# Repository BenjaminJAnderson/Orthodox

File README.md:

# ORTHODOX

A custom ortholinear mechanical keyboard comprising a 60-key, two-layer PCB designed in KiCad, a FreeCAD case and parametric OpenSCAD keycaps. The design uses Kailh Choc switches, per-key diodes and USB-C, with copper coil footprints reserved for future analogue sensing.

## Overview

Orthodox is a design archive for a compact ortholinear keyboard. Its grid layout removes the row offsets of a conventional staggered keyboard, simplifying both the keycap geometry and the electrical matrix. The repository contains the KiCad schematic and PCB, manufacturing exports, a FreeCAD case model and a parametric keycap generator.

This repository covers the hardware and mechanical design. Firmware is not included, the LDC1614 inductive-sensing circuit is planned but not present on this PCB revision, and no fabrication, assembly or measurement results are recorded. The files are useful as a reference design or starting point for further work, not as a verified build guide.

## Features

- **60-key ortholinear matrix:** thirteen columns and five rows, including 2u keys, a 6u spacebar and smaller 0.5u keycaps.
- **Per-key diodes:** sixty 1206 surface-mount diodes, one for each switch position.
- **ATmega32U4 controller:** a TQFP-44 ATmega32U4-A with a four-pad crystal, reset circuit and decoupling.
- **USB-C connection:** a GCT USB4055-30-A receptacle wired for USB 2.0 data and power.
- **Kailh Choc footprints:** 1u, 2u and 6u switch positions using Kailh Choc V1 footprints, plus compact 58-series footprints for the smallest keys.
- **Coil-enabled key positions:** eight switch footprints on W, A, S, D and the four arrow keys include dual-layer copper spirals for future inductive sensing.
- **Two-layer PCB:** 1.6 mm FR4, approximately 253.15 x 100.75 mm, with 467 routed track segments and 23 vias.
- **Manufacturing exports:** Gerber, drill and job files in `Hardware/PCB/export/`, plus a STEP model of the board.
- **FreeCAD case model:** a Part Design body measuring approximately 259.26 x 107 x 20 mm.
- **Parametric keycaps:** a KeyV2-based OpenSCAD generator with per-key positions, sizes, heights and five legend layers.
- **Coil generator:** a Python script that emits KiCad track segments for the spiral coils.

## Technologies

- **KiCad:** schematic capture, PCB layout, design rules, 3D preview and Gerber generation.
- **FreeCAD:** parametric case modelling with sketches, pads, pockets and chamfers.
- **OpenSCAD and KeyV2:** parametric keycap geometry, legends and STL export.
- **Python 3:** generation of the Archimedean spiral tracks used by the coil footprints.
- **ATmega32U4:** the USB-capable AVR microcontroller at the centre of the board.
- **Kailh Choc V1 and 58-series switches:** switch footprints used by the PCB.
- **USB-C:** the board's power and data connector.
- **LDC1614 (planned):** the intended inductive-sensing device for the coil-equipped keys, not yet implemented on the PCB.

## Gallery

The PCB layout shows the 13-column matrix, eight spiral coil footprints, the ATmega32U4 and the USB-C connector.

The schematic covers the USB-C interface, crystal, reset circuit, decoupling and the ATmega32U4 pin assignments.

The matrix uses thirteen column nets and five row nets, with one diode per switch.

The keycap layout includes mixed key sizes, smaller 0.5u keys and multiple legend positions.

The FreeCAD case model provides the outer enclosure around the PCB and keycap assembly.

## Technical details

### PCB and matrix

The board uses thirteen column nets, `COL0` to `COL12`, and five row nets, `ROW0` to `ROW4`, with one 1206 diode in series with each switch. Sixty switch positions are placed in the layout. The controller is an ATmega32U4-A in a TQFP-44 package. USB-C is wired for USB 2.0, with 22R series resistors on the data lines, a crystal with 22 pF load capacitors, a reset switch and a 10 kΩ pull-up on the reset line.

The board is a two-layer, 1.6 mm FR4 design measuring approximately 253.15 x 100.75 mm. The routed board contains 467 track segments and 23 vias. An online view of the board is available on [CADLAB.io](https://cadlab.io/project/25013).

### Inductive coil footprints

Eight switch positions, covering W, A, S, D and the four arrow keys, use special footprints containing a copper spiral around the switch centre. The spiral is drawn on both copper layers and uses 0.15 mm tracks with 0.30 mm spacing over eight turns. Each footprint adds two small SMD pads, numbered 3 and 4, for the coil terminals.

`Software/spiral.py` generates the spiral as individual KiCad `segment` entries and prints them to standard output. The radius, number of sides, track width, track spacing, turn count and layer can be changed at the bottom of the script. The design stops at the coil footprint: the schematic includes a two-pin `Coil` connector (`J2`), but no LDC1614 or other inductive-sensing IC is placed on the board.

### Case

`Hardware/Model/Keyboard/Keyboard.FCStd` contains a FreeCAD Part Design body with a sketch, pad, pocket and chamfer. Its outer envelope is approximately 259.26 x 107 x 20 mm. The repository does not include separate fabrication drawings or fit measurements for the case.

### Keycaps

`Hardware/Model/Keycaps/OrthodoxLayout.scad` is built on [KeyV2](https://github.com/rsheldiii/openSCAD-projects). It defines the position, width, height and legend of every key using explicit arrays, including the 2u keys, 6u spacebar and 0.5u keys. Five nested `legend()` calls place primary, function-key, symbol and shift legends at different positions on each keycap.

The layout uses the low-profile transformation, bar supports, an 18.16 mm base width and a nominal 11.5 mm total depth before the low-profile transformation. The included `OrthodoxLayout.stl` is a pre-exported model spanning approximately 247 x 94 x 8 mm. The layout file contains a commented `$stem_type = "choc"` setting; uncomment it before export to generate stems for the Choc switches.

## Challenges and solutions

### Integrating coils into switch footprints

- **Problem:** The analogue keys need a planar coil under each switch, but the switch cutout, central hole and electrical pads occupy the middle of the footprint.
- **Approach:** `spiral.py` generates the coil as many short KiCad track segments. These are embedded directly in a modified Kailh Choc footprint, using a larger pad arrangement and a spiral that surrounds the switch centre on both copper layers.
- **Outcome:** Eight coil-enabled footprints exist in the PCB layout. The sensing IC and its supporting circuit remain unbuilt, so the coil geometry has not been electrically validated.

### Placing multiple legends on small keycaps

- **Problem:** KeyV2's `legend()` module is designed around a single legend per keycap, while the Orthodox layout needs several legends on many keys.
- **Approach:** The layout nests five `legend()` calls with separate arrays for the centre, bottom-left, bottom-right, top-left and top-right positions. Font sizes and offsets are defined per key, including the smaller 0.5u keys.
- **Outcome:** A single OpenSCAD file produces the full 60-key layout and an STL export. The commit history records an attempt to add Font Awesome glyphs and notes that multiple-font rendering still needed investigation.

### Mixing key sizes in a regular grid

- **Problem:** An ortholinear grid is regular, but the design mixes 1u, 2u, 6u and 0.5u keys, so a single uniform array cannot describe the layout.
- **Approach:** The keycap generator stores explicit x/y positions, widths and heights for every key, with separate arrays for legends and font sizes. The PCB uses matching switch footprints and positions for the 2u, 6u and compact keys.
- **Outcome:** The layout and STL include the mixed key sizes. No physical fit test is recorded in the repository.

## Validation status

No fabricated board, assembly photographs, bill of materials or electrical measurements are included. A design rule check (DRC) run using KiCad 10.0.7 on `Hardware/PCB/Orthodox.kicad_pcb` reports 10 unconnected items and additional clearance, footprint, solder-mask and other violations, so the design should be reviewed and cleaned up before manufacture. The case and keycap models have not been physically validated for fit in this repository.

## Getting started

### Prerequisites

- KiCad 6 or newer for the schematic and PCB (the files use the KiCad 6 format).
- FreeCAD for the case model.
- OpenSCAD for the keycap generator.
- Python 3 for the coil generator.
- A PCB fabricator if manufacturing the board.

### Opening the design

```bash
git clone https://github.com/BenjaminJAnderson/Orthodox.git
cd Orthodox
```

Open `Hardware/PCB/Orthodox.kicad_pro` in KiCad to inspect the schematic and PCB. Open `Hardware/Model/Keyboard/Keyboard.FCStd` in FreeCAD for the case, and `Hardware/Model/Keycaps/OrthodoxLayout.scad` in OpenSCAD for the keycaps.

### Generating a coil

```bash
python3 Software/spiral.py
```

The script prints KiCad `segment` entries to standard output. Adjust the parameters at the bottom of the script, then paste the output into the PCB or a footprint as required.

### Exporting keycaps

```bash
openscad Hardware/Model/Keycaps/OrthodoxLayout.scad -o OrthodoxLayout.stl
```

The repository also includes a pre-exported `Hardware/Model/Keycaps/OrthodoxLayout.stl`.

### Manufacturing files

Gerber and drill files are in `Hardware/PCB/export/`. The STEP model of the board is `Hardware/PCB/Orthodox.step`. No firmware or flashing instructions are provided.

## Roadmap

- [ ] Integrate the LDC1614 sensing circuit and connect the eight coil footprints.

## Project structure

```text
Orthodox/
├── Hardware/
│   ├── PCB/
│   │   ├── Orthodox.kicad_pro / .kicad_sch / .kicad_pcb
│   │   ├── export/            # Gerbers, drill files and job file
│   │   ├── footprints/        # Kailh Choc and USB footprints
│   │   ├── resources/         # Datasheets and vendor references
│   │   └── references/        # Third-party keyboard designs
│   └── Model/
│       ├── Keyboard/          # FreeCAD case model
│       └── Keycaps/           # KeyV2 generator and Orthodox layout
├── Software/
│   └── spiral.py              # Coil track generator
├── docs/images/               # README images
└── README.md
```

## Credits and licensing

No licence file is currently included with this repository. The original design files remain the copyright of the author; contact the author through the repository for reuse permission.

Third-party components retain their own licences:

- **KeyV2** by rsheldiii is licensed under GPL-3.0; the keycap generator in `Hardware/Model/Keycaps/` is derived from it.
- **scad-utils** by Oskar Linde is licensed under the MIT licence; see `Hardware/Model/Keycaps/src/libraries/scad-utils/LICENSE`.
- **Round Anything** (`polyround.scad`) is licensed under the MIT licence.
- **Kailh Choc V1 footprints** are licensed under CC-BY-SA 4.0 with the exception stated in `Hardware/PCB/footprints/Kailh-Choc-V1/LICENSE`.
- **Reference designs** in `Hardware/PCB/references/` are third-party projects and retain their own licences; consult the licence and README files supplied with each project where present.
- **Datasheets** in `Hardware/PCB/resources/` remain the copyright of their respective manufacturers.

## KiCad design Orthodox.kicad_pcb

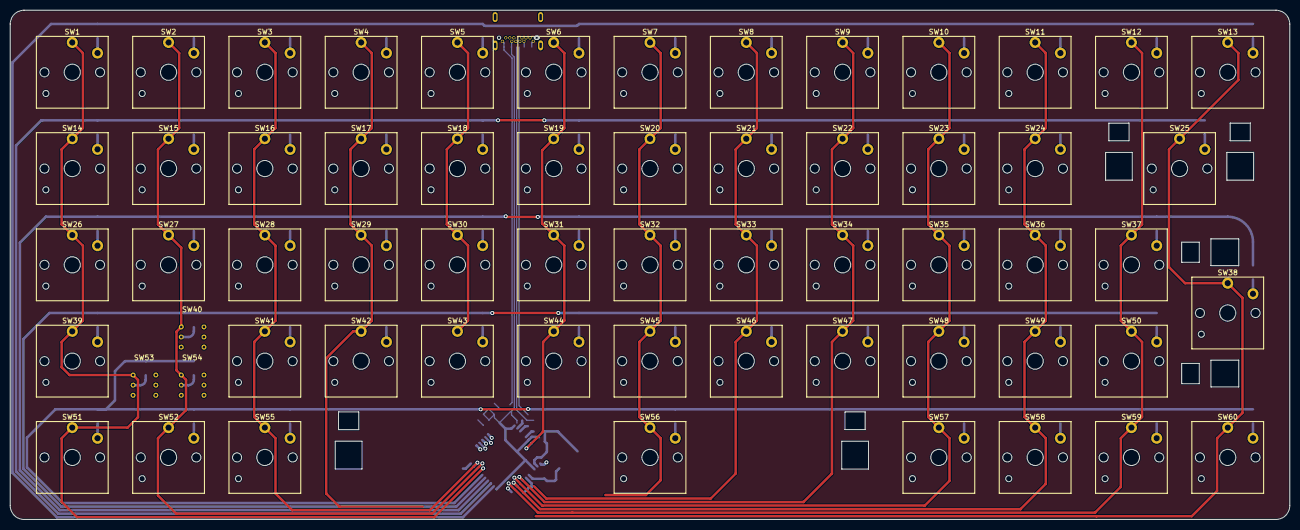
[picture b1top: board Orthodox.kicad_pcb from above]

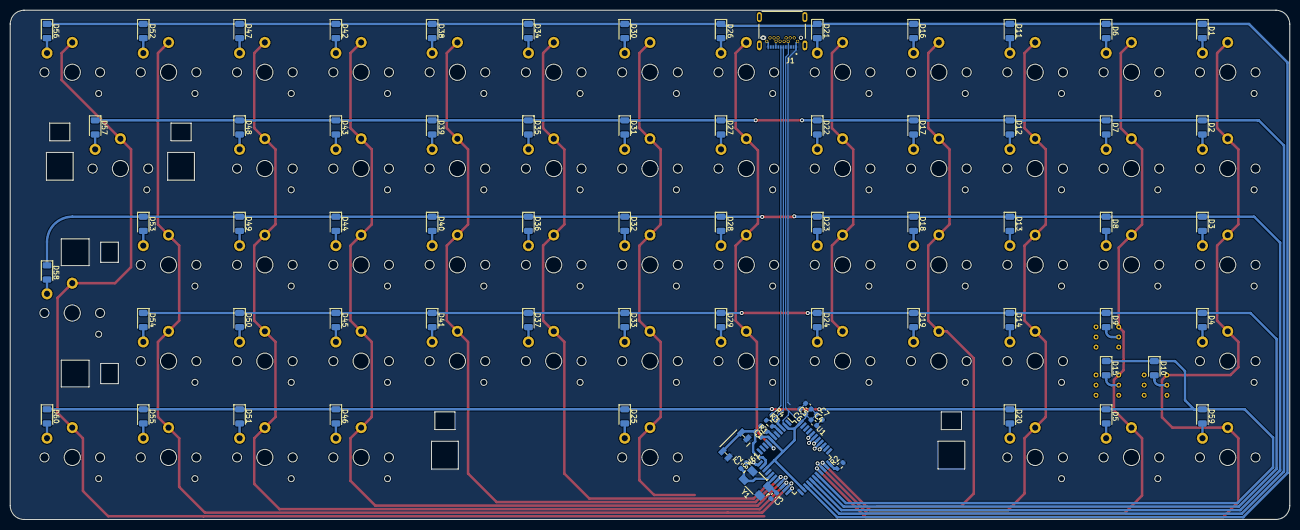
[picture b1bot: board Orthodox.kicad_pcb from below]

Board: 2 copper layers, 253.1 x 100.7 mm, 135 parts (75 on the bottom side), 89 nets.

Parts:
C1, C4, C5, C6, C7: C; C_0603_1608Metric
C2, C3: 22p; C_0603_1608Metric
D1, D2, D3, D4, D5, D6, D7, D8, D9, D10, D11, D12, D13, D14, D15, D16, D17, D18, D19, D20, D21, D22, D23, D24, D25, D26, D27, D28, D29, D30, D31, D32, D33, D34, D35, D36, D37, D38, D39, D40, D41, D42, D43, D44, D45, D46, D47, D48, D49, D50, D51, D52, D53, D54, D55, D56, D57, D58, D59, D60: D; D_1206_3216Metric
J1: USB_C_Receptacle_USB2.0; GCT_USB4055-30-A
R1, R2: 10k; R_0603_1608Metric
R3, R4: 22R; R_0603_1608Metric
SW1, SW2, SW3, SW4, SW5, SW6, SW7, SW8, SW9, SW10, SW11, SW12, SW13, SW14, SW15, SW16, SW17, SW18, SW19, SW20, SW21, SW22, SW23, SW24, SW26, SW27, SW28, SW29, SW30, SW31, SW32, SW33, SW34, SW35, SW36, SW37, SW39, SW41, SW42, SW43, SW44, SW45, SW46, SW47, SW48, SW49, SW50, SW51, SW52, SW55, SW57, SW58, SW59, SW60: SW_Push; SW_Kailh_Choc_V1_1.00u
SW25: SW_Push; SW_Kailh_Choc_V1_2.00u
SW38: SW_Push; SW_Kailh_Choc_V1_2.00u_Rotated
SW40: RED; SW_58_Series_Kalih
SW53: BLUE; SW_58_Series_Kalih
SW54: GREEN; SW_58_Series_Kalih
SW56: SW_Push; SW_Kailh_Choc_V1_6.00u_Offset
SW61: SW_Push; Panasonic_EVQPUJ_EVQPUA
U1: ATmega32U4-A; TQFP-44_10x10mm_P0.8mm
Y1: Crystal_GND24; Crystal_SMD_0603-4Pin_6.0x3.5mm

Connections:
+5V: C4.1, C5.1, C6.1, C7.1, J1.A4 (VBUS), J1.A9 (VBUS), J1.B4 (VBUS), J1.B9 (VBUS), R1.2, U1.2 (UVCC), U1.7 (VBUS), U1.14 (VCC), U1.24 (AVCC), U1.34 (VCC), U1.44 (AVCC)
COL0: SW1.1, SW14.1, SW26.1, SW39.1, SW51.1, SW53.1, U1.30 (PB6)
COL1: SW2.1, SW15.1, SW27.1, SW40.1, SW52.1, SW54.1, U1.31 (PC6)
COL2: SW3.1, SW16.1, SW28.1, SW41.1, SW55.1, U1.32 (PC7)
COL3: SW4.1, SW17.1, SW29.1, SW42.1, U1.36 (PF7)
COL4: SW5.1, SW18.1, SW30.1, SW43.1, U1.37 (PF6)
COL5: SW6.1, SW19.1, SW31.1, SW44.1, U1.8 (PB0)
COL6: SW7.1, SW20.1, SW32.1, SW45.1, SW56.1, U1.41 (PF0)
COL7: SW8.1, SW21.1, SW33.1, SW46.1, U1.12 (PB7)
COL8: SW9.1, SW22.1, SW34.1, SW47.1, U1.18 (PD0)
COL9: SW10.1, SW23.1, SW35.1, SW48.1, SW57.1, U1.19 (PD1)
COL10: SW11.1, SW24.1, SW36.1, SW49.1, SW58.1, U1.20 (PD2)
COL11: SW12.1, SW37.1, SW50.1, SW59.1, U1.21 (PD3)
COL12: SW13.1, SW25.1, SW38.1, SW60.1, U1.22 (PD5)
D+: J1.A6 (D+), J1.B6 (D+), R3.1
D-: J1.A7 (D-), J1.B7 (D-), R4.1
GND: C1.2, C2.2, C3.2, C4.2, C5.2, C6.2, C7.2, J1.A1 (GND), J1.A12 (GND), J1.B1 (GND), J1.B12 (GND), R2.2, SW61.1, U1.5 (UGND), U1.15 (GND), U1.23 (GND), U1.35 (GND), U1.43 (GND), Y1.2, Y1.4
unnamed: C1.1, U1.6 (UCAP)
unnamed: D1.2 (A), SW1.2
unnamed: D2.2 (A), SW14.2
unnamed: D3.2 (A), SW26.2
unnamed: D4.2 (A), SW39.2
unnamed: D5.2 (A), SW52.2
unnamed: D6.2 (A), SW2.2
unnamed: D7.2 (A), SW15.2
unnamed: D8.2 (A), SW27.2
unnamed: D9.2 (A), SW40.2
unnamed: D10.2 (A), SW53.2
unnamed: D11.2 (A), SW3.2
unnamed: D12.2 (A), SW16.2
unnamed: D13.2 (A), SW28.2
unnamed: D14.2 (A), SW41.2
unnamed: D15.2 (A), SW54.2
unnamed: D16.2 (A), SW4.2
unnamed: D17.2 (A), SW17.2
unnamed: D18.2 (A), SW29.2
unnamed: D19.2 (A), SW42.2
unnamed: D20.2 (A), SW55.2
unnamed: D21.2 (A), SW5.2
unnamed: D22.2 (A), SW18.2
unnamed: D23.2 (A), SW30.2
unnamed: D24.2 (A), SW43.2
unnamed: D25.2 (A), SW56.2
unnamed: D26.2 (A), SW6.2
unnamed: D27.2 (A), SW19.2
unnamed: D28.2 (A), SW31.2
unnamed: D29.2 (A), SW44.2
unnamed: D30.2 (A), SW7.2
unnamed: D31.2 (A), SW20.2
unnamed: D32.2 (A), SW32.2
unnamed: D33.2 (A), SW45.2
unnamed: D34.2 (A), SW8.2
unnamed: D35.2 (A), SW21.2
unnamed: D36.2 (A), SW33.2
unnamed: D37.2 (A), SW46.2
unnamed: D38.2 (A), SW9.2
unnamed: D39.2 (A), SW22.2
unnamed: D40.2 (A), SW34.2
unnamed: D41.2 (A), SW47.2
unnamed: D42.2 (A), SW10.2
unnamed: D43.2 (A), SW23.2
unnamed: D44.2 (A), SW35.2
unnamed: D45.2 (A), SW48.2
unnamed: D46.2 (A), SW57.2
unnamed: D47.2 (A), SW11.2
unnamed: D48.2 (A), SW24.2
unnamed: D49.2 (A), SW36.2
unnamed: D50.2 (A), SW49.2
unnamed: D51.2 (A), SW58.2
unnamed: D52.2 (A), SW12.2
unnamed: D53.2 (A), SW37.2
unnamed: D54.2 (A), SW50.2
unnamed: D55.2 (A), SW59.2
unnamed: D56.2 (A), SW13.2
unnamed: D57.2 (A), SW25.2
unnamed: D58.2 (A), SW38.2
unnamed: D59.2 (A), SW51.2
unnamed: D60.2 (A), SW60.2
unnamed: R2.1, U1.33 (~HWB/PE2)
unnamed: R3.2, U1.4 (D+)
unnamed: R4.2, U1.3 (D-)
ROW0: D1.1 (K), D6.1 (K), D11.1 (K), D16.1 (K), D21.1 (K), D26.1 (K), D30.1 (K), D34.1 (K), D38.1 (K), D42.1 (K), D47.1 (K), D52.1 (K), D56.1 (K), U1.25 (PD4)
ROW1: D2.1 (K), D7.1 (K), D12.1 (K), D17.1 (K), D22.1 (K), D27.1 (K), D31.1 (K), D35.1 (K), D39.1 (K), D43.1 (K), D48.1 (K), D57.1 (K), U1.26 (PD6)
ROW2: D3.1 (K), D8.1 (K), D13.1 (K), D18.1 (K), D23.1 (K), D28.1 (K), D32.1 (K), D36.1 (K), D40.1 (K), D44.1 (K), D49.1 (K), D53.1 (K), D58.1 (K), U1.27 (PD7)
ROW3: D4.1 (K), D9.1 (K), D14.1 (K), D19.1 (K), D24.1 (K), D29.1 (K), D33.1 (K), D37.1 (K), D41.1 (K), D45.1 (K), D50.1 (K), D54.1 (K), U1.28 (PB4)
ROW4: D5.1 (K), D10.1 (K), D15.1 (K), D20.1 (K), D25.1 (K), D46.1 (K), D51.1 (K), D55.1 (K), D59.1 (K), D60.1 (K), U1.29 (PB5)
Reset: R1.1, SW61.2, U1.13 (~RESET)
XTAL1: C3.1, U1.17 (XTAL1), Y1.1
XTAL2: C2.1, U1.16 (XTAL2), Y1.3

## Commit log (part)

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2021-12-15 Backlink to CADLAB.io has been added.
2021-12-15 Added FIles for Orthodox PCB
2022-02-11 Updated to V6 and used fillets
2022-02-18 Half way through cleaning up keyswitch models and placement
2022-02-18 Cleaned up
2022-02-19 Test commit
2022-02-19 Cleanup, reference designs and sticking with atmega
2022-02-22 Rought placement of mounting holes + routing
2022-10-05 Reorganised files and added keycap code
2022-10-05 Added all keys with rough layout
2022-10-06 improving layouts
2022-10-06 finished layout, just need to make keycaps for smaller pieces and shift
2022-10-06 finished layout and made rough shape for key, nice if we could round the inner corner like before
2022-10-07 added export and freecad model which will have keyboard design
2022-10-16 tried adding fontawesome icons to openscad, need to try doing multiple fonts
2022-10-29 Edited folders to be clearer, added 1st draft of coil to WSAD + ARROW.
